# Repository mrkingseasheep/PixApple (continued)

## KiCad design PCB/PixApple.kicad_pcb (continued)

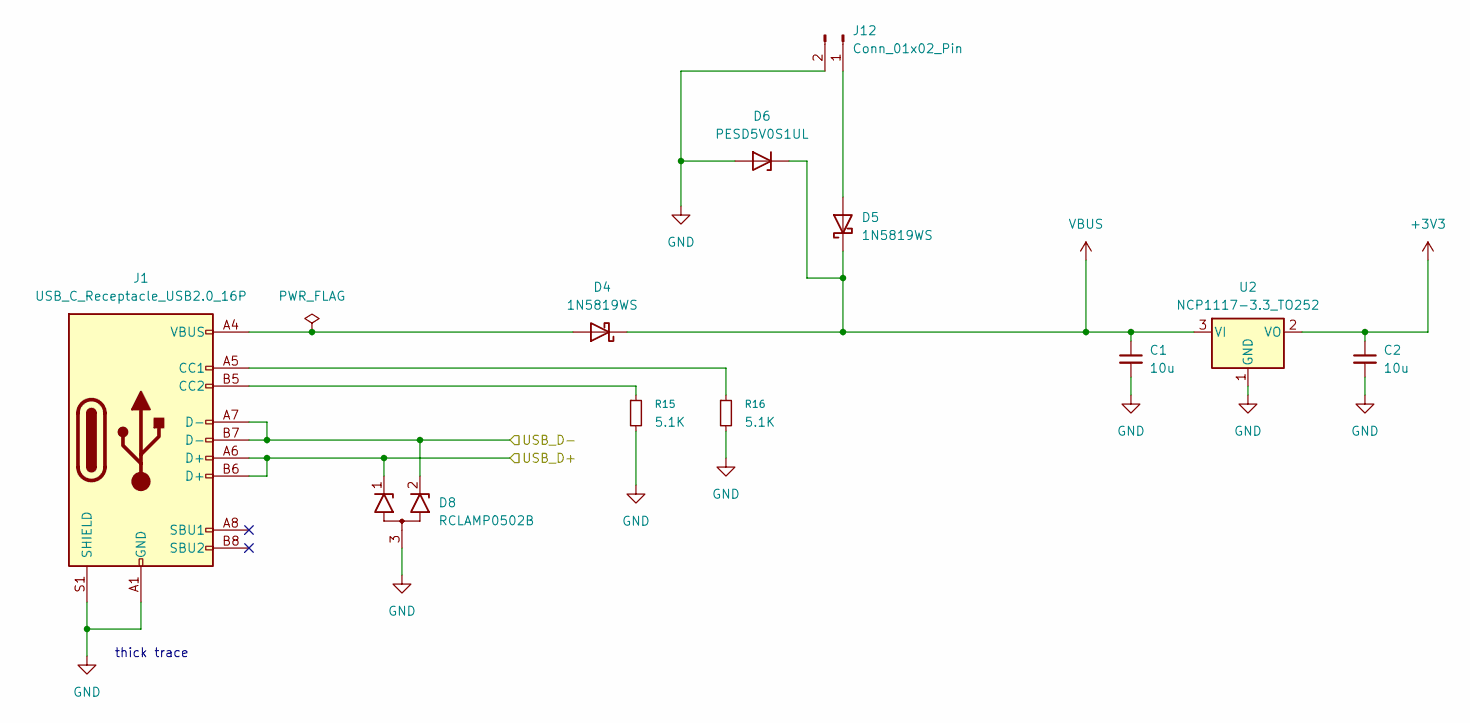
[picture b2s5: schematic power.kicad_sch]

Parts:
C1, C2: 10u; C_0603_1608Metric_Pad1.08x0.95mm_HandSolder
D4, D5: 1N5819WS; D_SOD-323
D6: PESD5V0S1UL; D_SOD-882
D8: RCLAMP0502B; SOT-416
J1: USB_C_Receptacle_USB2.0_16P; USB_C_Receptacle_GCT_USB4105-xx-A_16P_TopMnt_Horizontal
J12: Conn_01x02_Pin; PinHeader_1x02_P2.54mm_Vertical
R15, R16: 5.1K; R_0603_1608Metric_Pad0.98x0.95mm_HandSolder
U2: NCP1117-3.3_TO252; TO-252-2

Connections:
+3V3: C2.1, U2.2 (VO); also elsewhere on the board
/usb/USB_D+: D8.1 (K1), J1.A6 (D+), J1.B6 (D+); also elsewhere on the board
/usb/USB_D-: D8.2 (K2), J1.A7 (D-), J1.B7 (D-); also elsewhere on the board
GND: C1.2, C2.2, D6.2 (A), D8.3 (A), J1.A1 (GND), J1.A12 (GND), J1.B1 (GND), J1.B12 (GND), J1.S1 (SHIELD), J12.2, R15.2, R16.2, U2.1 (GND); also elsewhere on the board
unnamed: D4.2 (A), J1.A4 (VBUS), J1.A9 (VBUS), J1.B4 (VBUS), J1.B9 (VBUS)
unnamed: D5.2 (A), J12.1
unnamed: J1.A5 (CC1), R16.1
unnamed: J1.B5 (CC2), R15.1
VBUS: C1.1, D4.1 (K), D5.1 (K), D6.1 (K), U2.3 (VI); also elsewhere on the board

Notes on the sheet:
thick trace

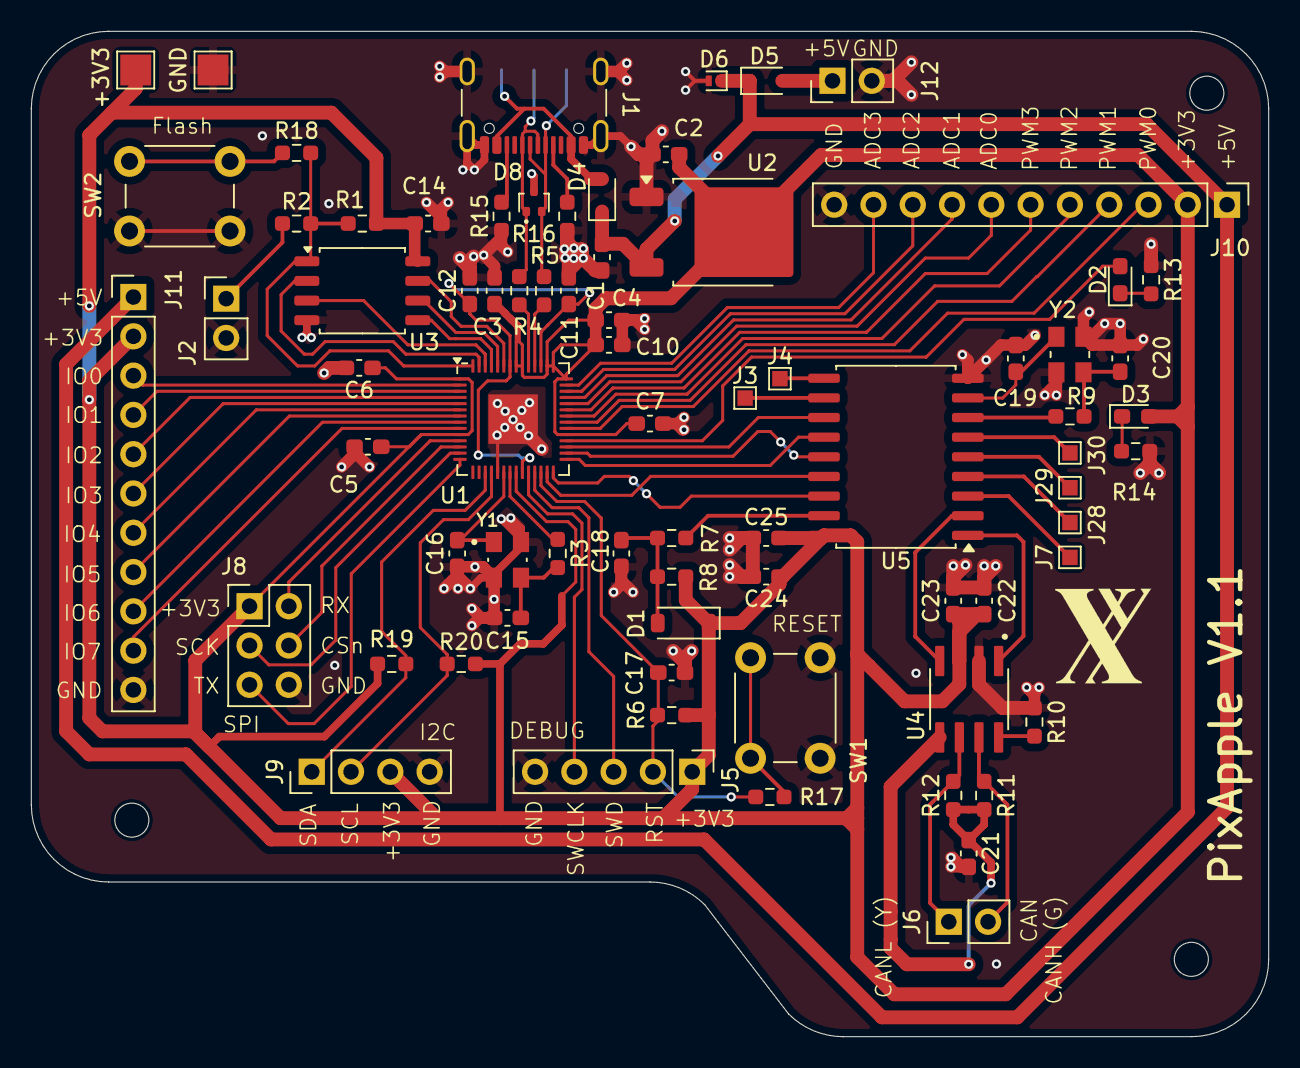
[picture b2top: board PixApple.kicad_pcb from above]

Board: 2 copper layers, 80.0 x 65.0 mm, 75 parts (0 on the bottom side), 74 nets.

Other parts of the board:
+3V3: TestPoint_Pad_2.0x2.0mm
GND: TestPoint_Pad_2.0x2.0mm

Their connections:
+3V3: +3V3.1; also elsewhere on the board
GND: GND.1; also elsewhere on the board

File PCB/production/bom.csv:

Designator,Footprint,Quantity,Value,LCSC Part #
"C1, C2",0603,2,10u,
"C10, C11, C23, C25",0603,4,1u,
"C12, C14, C17, C18, C22, C24, C3, C4, C5, C6, C7",0603,11,100n,
"C15, C16",0603,2,15p,
"C19, C20",0603,2,30p,
C21,0603,1,4.7n,
D1,D_SOD-123,1,1N4148W,
"D2, D3",0603,2,LED_Small,
"D4, D5",D_SOD-323,2,1N5819WS,
J1,USB_C_Receptacle_GCT_USB4105-xx-A_16P_TopMnt_Horizontal,1,USB_C_Receptacle_USB2.0_16P,
"J10, J11",PinHeader_1x11_P2.54mm_Vertical,2,Conn_01x11,
"J12, J2, J6",PinHeader_1x02_P2.54mm_Vertical,3,Conn_01x02_Pin,
"J28, J29, J3, J30, J4, J7",TestPoint_Pad_1.0x1.0mm,6,Conn_01x01_Pin,
J5,PinHeader_1x05_P2.54mm_Vertical,1,Conn_01x05_Pin,
J8,PinHeader_2x03_P2.54mm_Vertical,1,Conn_02x03_Odd_Even,
J9,PinHeader_1x04_P2.54mm_Vertical,1,Conn_01x04_Pin,
"R1, R10, R6, R8",0603,4,10k,
"R11, R12",0603,2,60R,
"R13, R14",0603,2,220R,
"R15, R16",0603,2,5.1K,
"R17, R18, R2, R3, R7, R9",0603,6,1k,
"R19, R20",0603,2,4.7K,
"R4, R5",0603,2,27R,
"SW1, SW2",SW_PUSH_6mm,2,SW_Push,
U1,QFN-56-1EP_7x7mm_P0.4mm_EP3.2x3.2mm,1,RP2040,
U2,TO-252-2,1,NCP1117-3.3_TO252,
U3,SOIC-8_5.3x5.3mm_P1.27mm,1,W25Q128JVS,
U4,SOIC127P599X175-8N,1,SN65HVD230DR,
U5,SOIC-18W_7.5x11.6mm_P1.27mm,1,MCP2515-xSO,
Y1,XTAL_ABM8-272-T3,1,ABM8-272-T3,
Y2,XTAL_ABM8-16.000MHZ-B2-T,1,ABM8-16.000MHZ-B2-T,

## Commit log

2025-07-05 Added journal
2025-07-06 MCP2515 design, kicad sucks
2025-07-07 CAN bus done?
2025-07-07 Organized
2025-07-08 Routing PCB
2025-07-09 Redo time, pcb too close
2025-07-09 PCB routing, better placement
2025-07-09 Finished PCB routing
2025-07-09 labeling done
2025-07-10 Writeup + case
2025-07-10 Case
2025-07-10 Final notes
2025-07-10 Parst csv
2025-07-10 BOM update
2025-07-10 parts update
2025-07-10 Formating
2025-07-10 Updated values
2025-07-10 Fix pullup, connected 3V3 completely
2025-07-10 esd, pullup, error fix
2025-07-10 Fixed
2025-07-12 Completely new setup omg
2025-07-13 BOM will finish soon
2025-07-13 New bom
2025-07-13 BOM done
2025-07-13 added step files
2025-07-13 BOM changes
2025-07-13 add pcb to prod
